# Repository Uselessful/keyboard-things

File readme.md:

I take zero responsibility for the designs published here. Most of them weren't even implemented as prototypes. Use at your own risk.

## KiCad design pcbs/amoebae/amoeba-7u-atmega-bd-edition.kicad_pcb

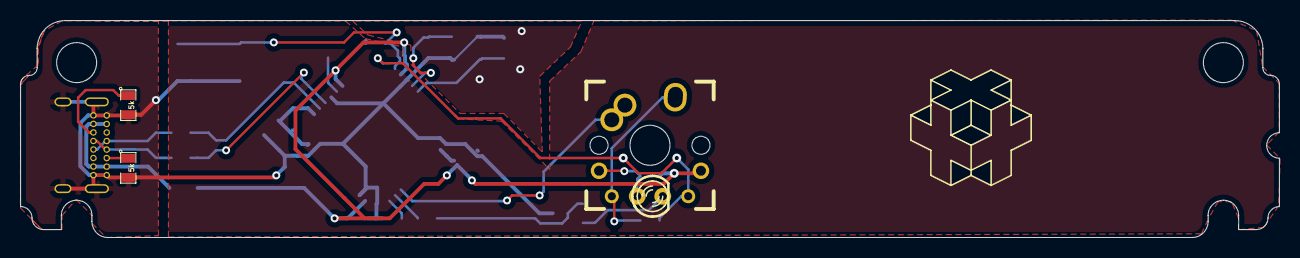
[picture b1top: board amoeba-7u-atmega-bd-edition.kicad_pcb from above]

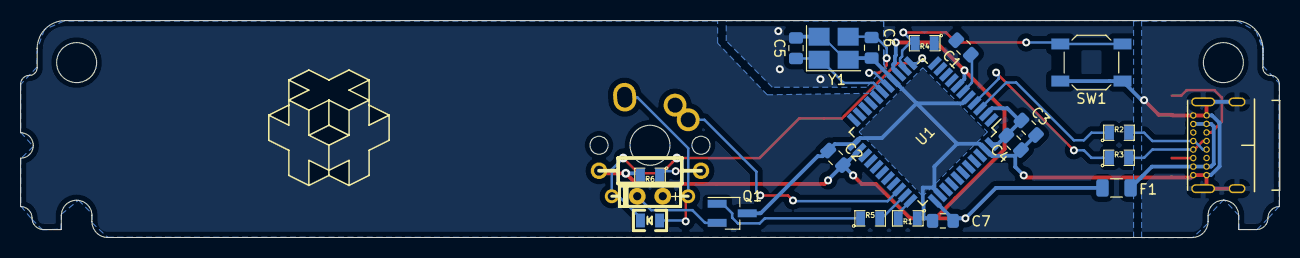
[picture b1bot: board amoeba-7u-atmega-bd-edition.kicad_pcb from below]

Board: 2 copper layers, 125.5 x 21.6 mm, 25 parts (21 on the bottom side), 16 nets.

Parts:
5k, 5k#2: RESISTOR; SM0805
C1: 1uF; C_0805_2012Metric_Pad1.15x1.40mm_HandSolder
C2, C3, C4: 0.1uF; C_0805_2012Metric_Pad1.15x1.40mm_HandSolder
C5, C6: 22pF; C_0805_2012Metric_Pad1.15x1.40mm_HandSolder
C7: 10uF; C_0805_2012Metric_Pad1.15x1.40mm_HandSolder
D0: DIODE; D3
D1: DIODE; SM0805D
F1: Fuse_1206_3216Metric
LED0: LED; LED-3MM
Q1: Q_NMOS_GDS; SOT-23_Handsoldering
R0: RESISTOR
R1, R2, R3, R4, R5, R6: RESISTOR; SM0805
S0: MX1A; ALPS_CHERRY_ZEAL_PCB_100H
SW1: SW_PUSH; SW_SPST_SKQG_WithStem
U1: ATmega32U4-AU; TQFP-44_10x10mm_P0.8mm
Y1: 16MHz; Crystal_SMD_3225-4Pin_3.2x2.5mm_HandSoldering

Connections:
+5V: C2.1, C3.1, C4.1, C7.1, F1.1, R0.2, R4.1, R6.2, U1.2, U1.7, U1.14, U1.24, U1.34, U1.44
GND: 5k.2, 5k#2.2, C2.2, C3.2, C4.2, C5.2, C6.2, C7.2, Q1.3, R1.1, SW1.1, U1.5, U1.15, U1.23, U1.35, U1.43, Y1.2, Y1.4
LC0: LED0.2, Q1.2
N-LR0: LED0.1, R0.1, R6.1
N-SR0: D0.1, D1.1, S0.1
unnamed: C1.1, U1.6
unnamed: C5.1, U1.17, Y1.1
unnamed: C6.1, U1.16, Y1.3
unnamed: Q1.1, R5.1
unnamed: R1.2, U1.33
unnamed: R2.1, U1.3
unnamed: R3.1, U1.4
unnamed: R4.2, SW1.2, U1.13
PWM: R5.2, U1.32
SC0: S0.2, U1.31
SR0: D0.2, D1.2, U1.12

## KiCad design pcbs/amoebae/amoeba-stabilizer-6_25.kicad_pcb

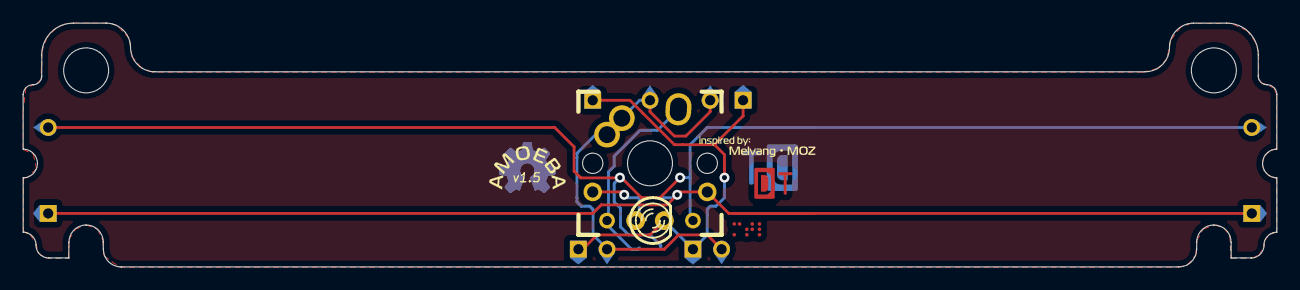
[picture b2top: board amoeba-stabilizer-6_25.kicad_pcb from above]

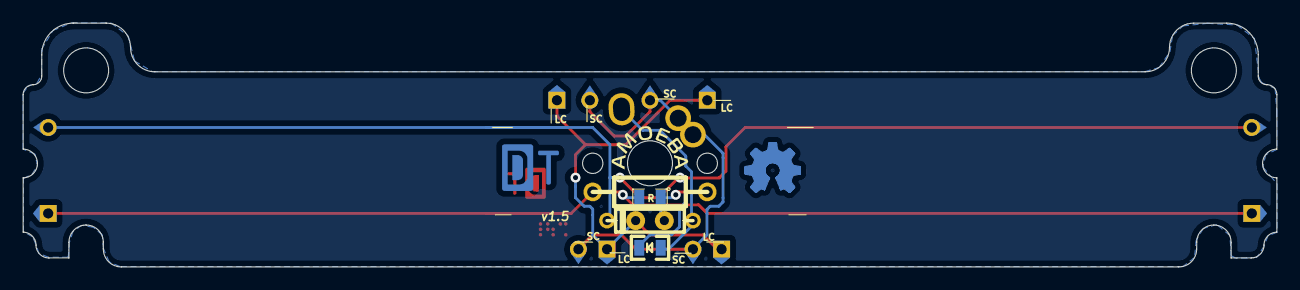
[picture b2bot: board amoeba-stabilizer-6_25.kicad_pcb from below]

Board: 2 copper layers, 111.2 x 21.6 mm, 38 parts (16 on the bottom side), 6 nets.

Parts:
D0: DIODE; D3
D1: DIODE; SM0805D
LC0:0, LC0:1, LC0:2, LC0:3: CONN_1; Pad
LED0: LED; LED-3MM
LR0:0, LR0:1: CONN_1; Pad
R0: RESISTOR
R1: RESISTOR; SM0805
S0: MX1A; ALPS_CHERRY_ZEAL_PCB_100H
SC0:0, SC0:1, SC0:2, SC0:3: CONN_1; Pad
SR0:0, SR0:1: CONN_1; Pad
amoeba-round: G***; amoeba-round
amoeba-round-rev: G***; amoeba-round-rev
dt-logo-big-rev: G***; dt-logo-big-rev
dt-logo-d: G***; dt-logo-d
dt-logo-t: G***; dt-logo-t
labels-melvang-moz: G***; labels-melvang-moz
mtl-braille: G***; mtl-braille
osh-logo-rev: G***; osh-logo-rev
pad-arrow-round: G***; pad-arrow-round
pad-arrow-round#2, pad-arrow-round#3, pad-arrow-round#4, pad-arrow-round#5, pad-arrow-round#6: G***; pad-arrow-round
pad-arrow-square: G***; pad-arrow-square
pad-arrow-square#2, pad-arrow-square#3, pad-arrow-square#4, pad-arrow-square#5, pad-arrow-square#6: G***; pad-arrow-square

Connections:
/key/LC0: LC0:0.1, LC0:1.1, LC0:2.1, LC0:3.1, LED0.2
/key/LR0: LR0:0.1, LR0:1.1, R0.2, R1.2
/key/SC0: S0.2, SC0:0.1, SC0:1.1, SC0:2.1, SC0:3.1
/key/SR0: D0.2, D1.2, SR0:0.1, SR0:1.1
/key/led/N-LR0: LED0.1, R0.1, R1.1
/key/switch/N-SD0: D0.1, D1.1, S0.1

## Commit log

2020-04-05 Added amoebae PCBs with long stab support
2020-04-07 Fix board outline
2020-04-07 Create gerbers folder
2020-04-07 Create archive for 7u amoeba gerber
2020-04-07 Fix board outline and SR0 track
2020-04-07 Create archive for 7u-promicro gerber
2020-04-07 Remove bak files
2020-04-08 Fix gerber files
2020-04-09 Added 2x1u board with USB-C port
2020-04-10 Added 4x4 keypad PCB files
2020-04-10 fix zone filling
2020-04-10 fix reset switch
2020-06-25 moved qmk folders to this repo
2020-06-25 Added license
2021-01-22 cleanup, qmk updates, uploaded the rest of 7u pcbs
2021-03-10 firmware updates
2021-11-01 Fixed number of rows/column mismatch, increased polling rate
2021-12-19 Create via
